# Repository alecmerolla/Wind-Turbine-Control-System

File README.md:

# Wind-Turbine-Control-System
Based on atmega328p in AVR for control of various wind turbine systems

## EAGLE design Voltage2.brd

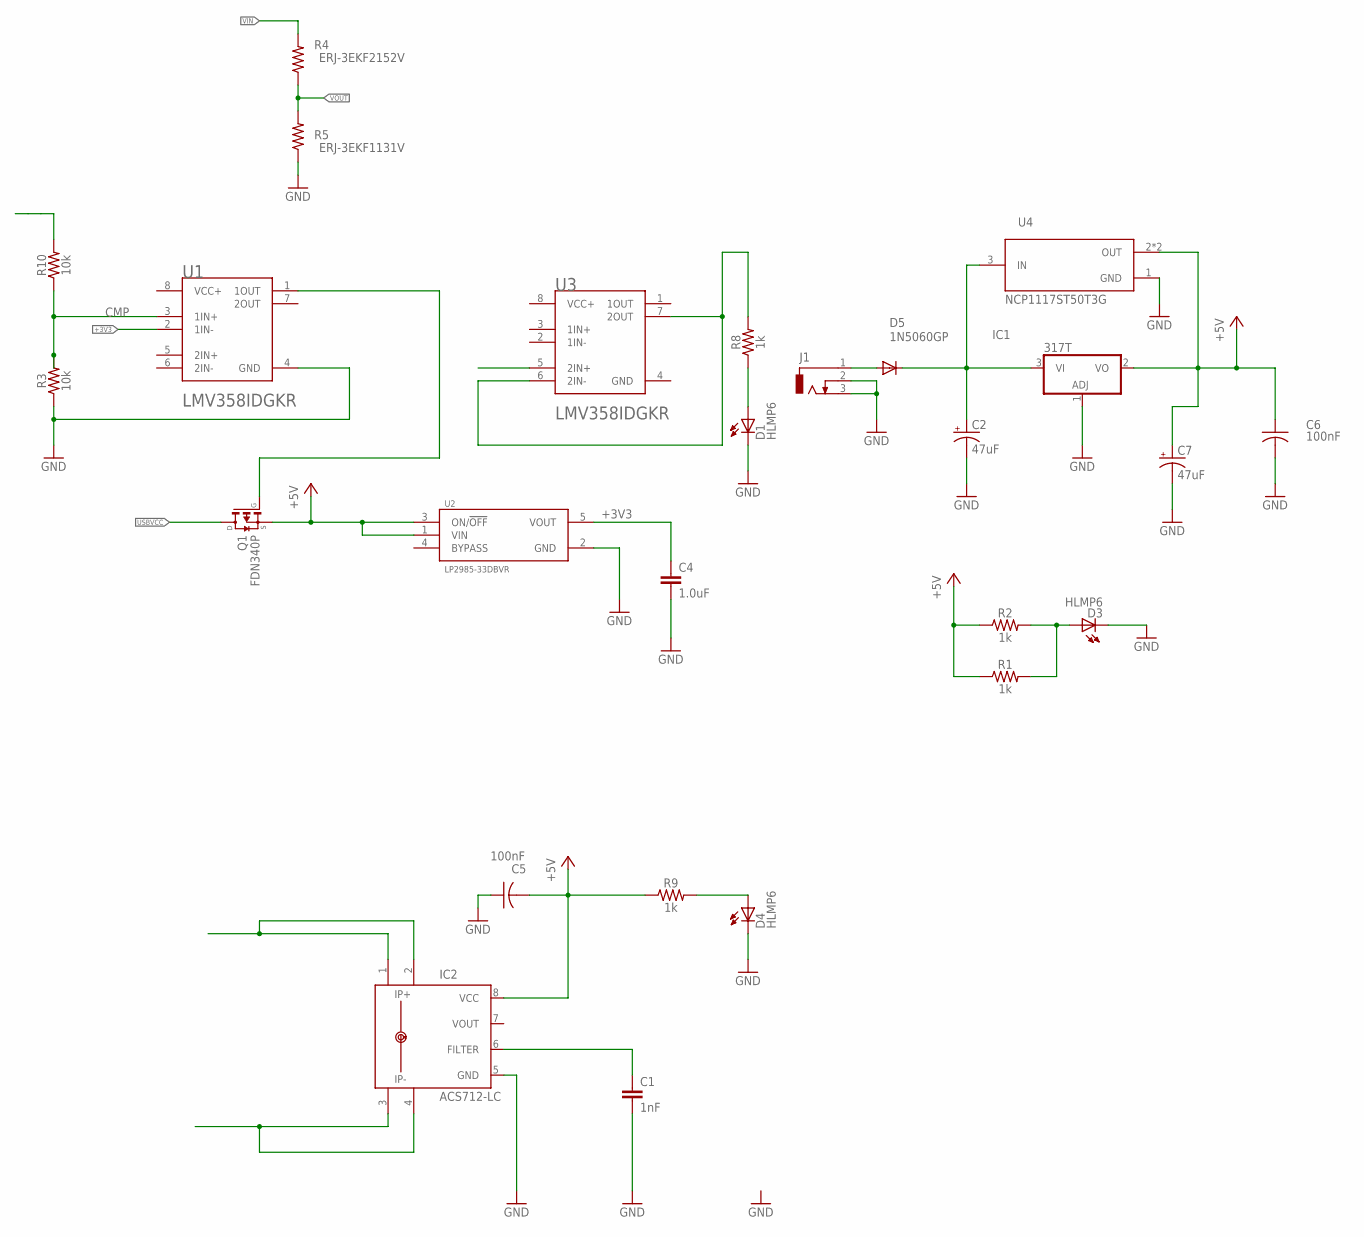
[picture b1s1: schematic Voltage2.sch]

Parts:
C1: 1nF; 0603
C2, C7: 47uF; EIA3528
C4: 1.0uF; 0603
C5, C6: 100nF; C0603
D1, D3, D4: HLMP6
D5: 1N5060GP; DO15-12
IC1: 317T; TO220H
IC2: ACS712-LC; SOIC8
J1: DCJ0303
Q1: FDN340P; SSOT-3
R1, R2, R8, R9: 1k; 0603
R3, R10: 10k; 0603
R4: ERJ-3EKF2152V; RESC1608X55
R5: ERJ-3EKF1131V; RESC1608X55
U1, U3: TEXAS_INSTRUMENTS_LMV358IDGKRTEXAS_INSTRUMENTS_LM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; TEXAS_INSTRUMENTS_LMV358IDGKR_0
U2: LP2985-33DBVR; SOT95P280X145-5N
U4: NCP1117ST50T3G; SOT230P700X180-4N

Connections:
1K: R8.2, U3.6 (2IN-), U3.7 (2OUT)
10K: R10.2
47U: C2.C (-)
100N: C6.1, C7.A (+), IC1.2 (VO), U4.2 (OUT), U4.4 (OUT)
+3V3: C4.1, U1.2 (1IN-), U2.5 (VOUT)
+5V: C5.2, IC2.8 (VCC), Q1.2 (S), R1.1, R2.1, R9.1, U2.1 (VIN), U2.3 (ON/!OFF)
CMP: R3.2, R10.1, U1.3 (1IN+)
GND: C1.2, C4.2, C5.1, C6.2, C7.C (-), D1.K, D3.K, D4.K, IC1.1 (ADJ), IC2.5 (GND), J1.2, J1.3, R3.1, R5.1, U1.4 (GND), U2.2 (GND), U4.1 (GND)
unnamed: D3.A, R1.2, R2.2
unnamed: Q1.1 (G), U1.1 (1OUT)
unnamed: D5.A, J1.1
unnamed: D4.A, R9.2
unnamed: D1.A, R8.1
unnamed: C2.A (+), D5.C, IC1.3 (VI), U4.3 (IN)
unnamed: C1.1, IC2.6 (FILTER)
unnamed: IC2.3 (IP-), IC2.4 (IP-1)
unnamed: IC2.1 (IP+), IC2.2 (IP+1)
USBVCC: Q1.3 (D)
VIN: R4.2
VOUT: R4.1, R5.2

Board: 2 copper layers, 26 parts (0 on the bottom side), 16 nets, no tracks yet.

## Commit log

2018-10-22 Create HD44780_Anemometer_ADC
2018-10-22 Rename HD44780_Anemometer_ADC to HD44780_Anemometer_ADC.c
2018-10-24 Create HD44780_Anemometer_ADC_Degrees
2018-10-31 Create RGB_AVR_TEST
2018-10-31 Create LCD Anemometer for Exam

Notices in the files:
parts and their libraries:
SparkFun-Resistors: Licensing: Creative Commons ShareAlike 4.0 International - https://creativecommons.org/licenses/by-sa/4.0
